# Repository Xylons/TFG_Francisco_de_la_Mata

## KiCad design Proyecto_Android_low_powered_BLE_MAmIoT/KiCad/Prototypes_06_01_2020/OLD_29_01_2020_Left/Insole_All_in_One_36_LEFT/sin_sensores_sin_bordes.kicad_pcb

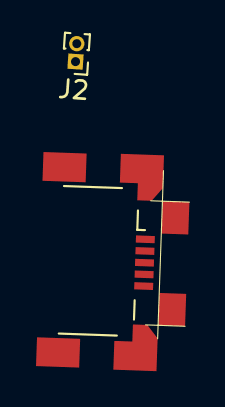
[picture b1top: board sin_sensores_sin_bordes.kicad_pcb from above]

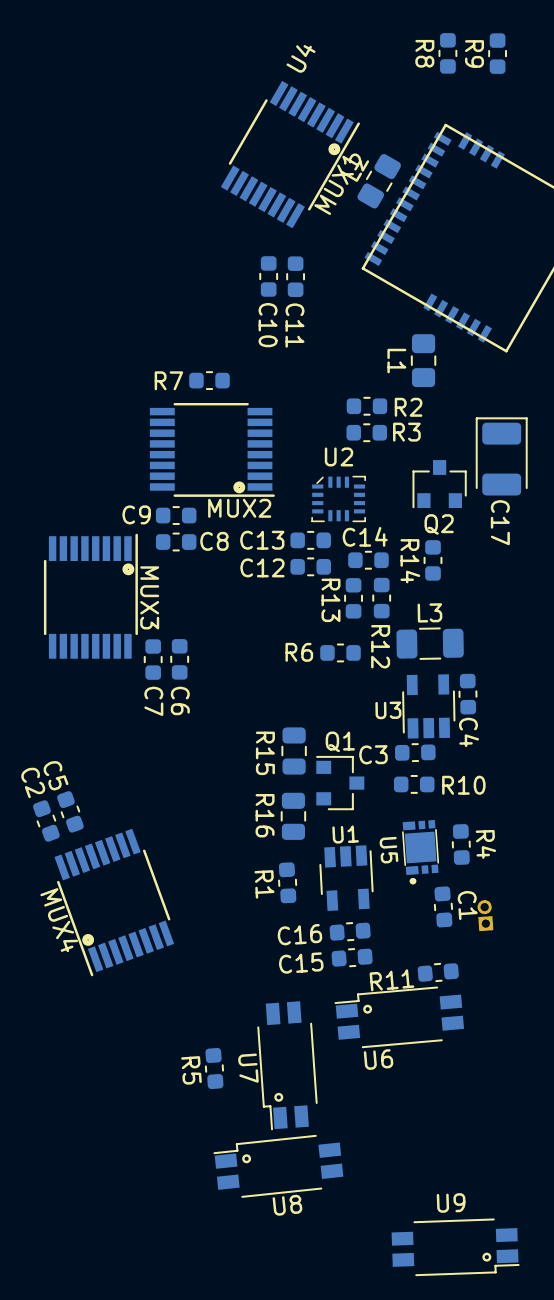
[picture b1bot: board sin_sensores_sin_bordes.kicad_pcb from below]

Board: 2 copper layers, 53 parts (51 on the bottom side), 34 nets, no tracks yet.

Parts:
C1, C5, C7, C9, C11, C13, C14, C16: 0.1uF; C_0603_1608Metric
C2, C6, C8, C10, C12, C15: 1uF; C_0603_1608Metric
C3: 4.7uF; C_0603_1608Metric
C4: 10uF; C_0603_1608Metric
C17: 100uF; CP_EIA-3528-12_Kemet-T
J1: Conn_Micro_USB; USB_Micro_CustomV2
J2: 3V7_Battery; PinHeader_1x02_P1.00mm_Vertical
L1, L2: 300ohm 100MHz; L_0805_2012Metric_Pad1.15x1.40mm_HandSolder
L3: 1uH; L_1206_3216Metric
MUX1, MUX2, MUX3, MUX4: CD74HC4051; TSSOP-16_4.4x5mm_P0.65mm
Q1, Q2: Q_PMOS_GSD; SOT-23
R1, R2, R3, R6, R7, R8, R9, R12, R13: 10k; R_0603_1608Metric
R4: 390 ohm; R_0603_1608Metric
R5: 0-1k; R_0603_1608Metric
R10: 2.7k; R_0603_1608Metric
R11: 100-500 ohm; R_0603_1608Metric
R14: 100k; R_0603_1608Metric
R15: 10k; R_0805_2012Metric
R16: 100k; R_0805_2012Metric
U1: STC4054-4.2; TSOT-23-5
U2: ISM330DLC; Bosch_LGA-14_3x2.5mm_P0.5mm
U3: ADP2108AUJ-3.3; TSOT-23-5
U4: CYBLE-222014-01
U5: AP9211SA-AN-HAC-7; AP9211SAACHAC7
U6, U7, U8, U9: TCMT1100; SOP-4_4.4x2.8mm_P1.27mm

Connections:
+3V3: C2.2, C4.1, C5.2, C6.2, C7.2, C8.2, C9.2, C10.2, C11.2, C12.2, C13.2, C17.1, L1.1, L2.1, L3.2, MUX1.3, MUX1.16, MUX2.3, MUX2.16, MUX3.3, MUX3.16, MUX4.3, MUX4.16, R2.1, R3.1, R11.2, U2.5, U2.8, U3.4, U6.4
+5V: C15.2, C16.2, J1.1, Q1.1, R15.2, R16.1, U1.4, U6.2
+BATT: J2.2, Q1.2, R4.1, R16.2, U1.3
-BATT: C1.2, C15.1, C16.1, J1.5, J1.6, J2.1, R1.2, U1.2, U5.1, U5.2
/+3V3_VDD: L2.2, U4.14
/+3V3_VDDR: L1.2, U4.5
/+BATT_CUT: C3.2, Q1.3, Q2.2, R14.1, U3.1, U3.3
/MUX_E: MUX1.6, MUX2.6, MUX3.6, MUX4.6, U4.7
/P0.6_USB: J1.3, U8.4
/P0.7_USB: J1.4, U9.4
/S0: MUX1.11, MUX2.11, MUX3.11, MUX4.11, U4.19
/S1: MUX1.10, MUX2.10, MUX3.10, MUX4.10, U4.20
/S2: MUX1.9, MUX2.9, MUX3.9, MUX4.9, U4.21
/U1_Data: R9.2, U4.18
/U2_Data: R8.2, U4.17
/U3_Data: R7.2, U4.16
/U4_Data: R6.2, U4.13
/XRES_USB: J1.2, U7.4
Analog_Batt_Lvl: C14.1, R12.2, R13.1, U4.4
Enable_Batt_Lvl: Q2.1, R14.2, U4.3
GND: C2.1, C3.1, C4.2, C5.1, C6.1, C7.1, C8.1, C9.1, C10.1, C11.1, C12.1, C13.1, C14.2, C17.2, MUX1.7, MUX1.8, MUX2.7, MUX2.8, MUX3.7, MUX3.8, MUX4.7, MUX4.8, R6.1, R7.1, R8.1, R9.1, R10.2, R13.2, R15.1, U2.1, U2.2, U2.3, U2.6, U2.7, U3.2, U4.1, U4.11, U5.6, U7.2, U8.2, U9.2
unnamed: C1.1, R4.2, U5.3
unnamed: L3.1, U3.5
unnamed: Q2.3, R12.1
unnamed: R1.1, U1.5
unnamed: R2.2, U2.14, U4.9
unnamed: R3.2, U2.13, U4.10
unnamed: R5.1, U7.1, U8.1, U9.1
unnamed: R5.2, U6.3
unnamed: R10.1, U5.5
unnamed: R11.1, U6.1
P0.6: U4.12, U8.3
P0.7: U4.8, U9.3
XRES: U4.15, U7.3
